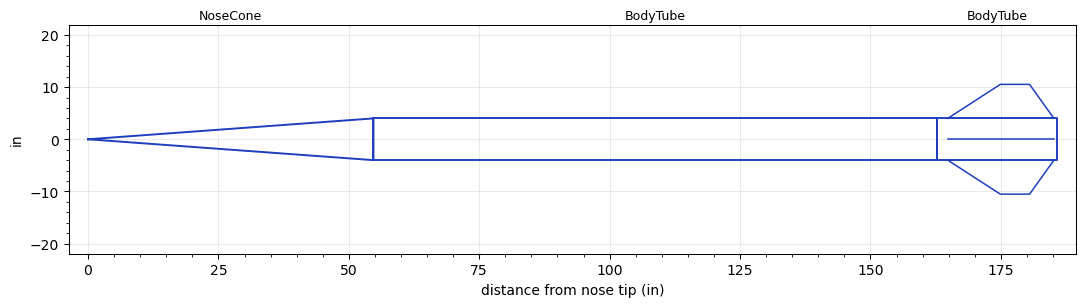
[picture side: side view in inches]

<RASAeroDocument>
 <FileVersion>2</FileVersion>
 <RocketDesign>
  <NoseCone>
   <Length>54.7243</Length>
   <Diameter>8</Diameter>
   <Shape>Conical</Shape>
   <Location>0</Location>
  </NoseCone>
  <BodyTube>
   <Length>107.9998</Length>
   <Diameter>8</Diameter>
   <Location>54.7243</Location>
  </BodyTube>
  <BodyTube>
   <Length>23</Length>
   <Diameter>8</Diameter>
   <Location>162.7241</Location>
   <Fin>
    <Count>4</Count>
    <Chord>20.3533</Chord>
    <Span>6.5203</Span>
    <SweepDistance>10.0728</SweepDistance>
    <TipChord>5.6197</TipChord>
    <Thickness>0.25</Thickness>
    <Location>20.9045</Location>
    <AirfoilSection>Square</AirfoilSection>
   </Fin>
  </BodyTube>
  <Surface>Rough Camouflage Paint</Surface>
  <CD>0</CD>
  <ModifiedBarrowman>False</ModifiedBarrowman>
  <Turbulence>False</Turbulence>
  <UseBooster1>False</UseBooster1>
  <UseBooster2>False</UseBooster2>
  <Comments>Testing for stability --&gt; upthrust sim</Comments>
 </RocketDesign>
 <LaunchSite>
  <Altitude>0</Altitude>
  <Pressure>29.9214</Pressure>
  <RodAngle>0</RodAngle>
  <RodLength>3.2808</RodLength>
  <Temperature>59</Temperature>
  <WindSpeed>4.4739</WindSpeed>
 </LaunchSite>
 <Recovery>
  <Altitude1>0</Altitude1>
  <Altitude2>0</Altitude2>
  <DeviceType1>None</DeviceType1>
  <DeviceType2>None</DeviceType2>
  <Event1>False</Event1>
  <Event2>False</Event2>
  <Size1>0</Size1>
  <Size2>0</Size2>
  <EventType1>None</EventType1>
  <EventType2>None</EventType2>
  <CD1>0</CD1>
  <CD2>0</CD2>
 </Recovery>
 <SimulationList>
  <Simulation>
   <SustainerLaunchWt>105.3169</SustainerLaunchWt>
   <SustainerCG>119.6624</SustainerCG>
   <SustainerIgnitionDelay>0</SustainerIgnitionDelay>
   <Booster1SeparationDelay>0</Booster1SeparationDelay>
   <Booster1IgnitionDelay>0</Booster1IgnitionDelay>
   <IncludeBooster1>False</IncludeBooster1>
   <Booster2Delay>0</Booster2Delay>
   <IncludeBooster2>False</IncludeBooster2>
  </Simulation>
 </SimulationList>
</RASAeroDocument>
